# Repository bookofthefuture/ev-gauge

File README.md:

# ev-gauge
SoC, motor amps, motor/pack temp, 12V aux voltage, car mode and Zombieverter error
data over CANbus, on a single mode-aware display. For ESP32.

Copy `ev_gauge/secrets.h.example` to `ev_gauge/secrets.h` and fill in your home WiFi
SSID/password before flashing - the gauge runs its own `gaugedriver` AP and joins that
network at the same time, so OTA updates work both standalone and from your desk.

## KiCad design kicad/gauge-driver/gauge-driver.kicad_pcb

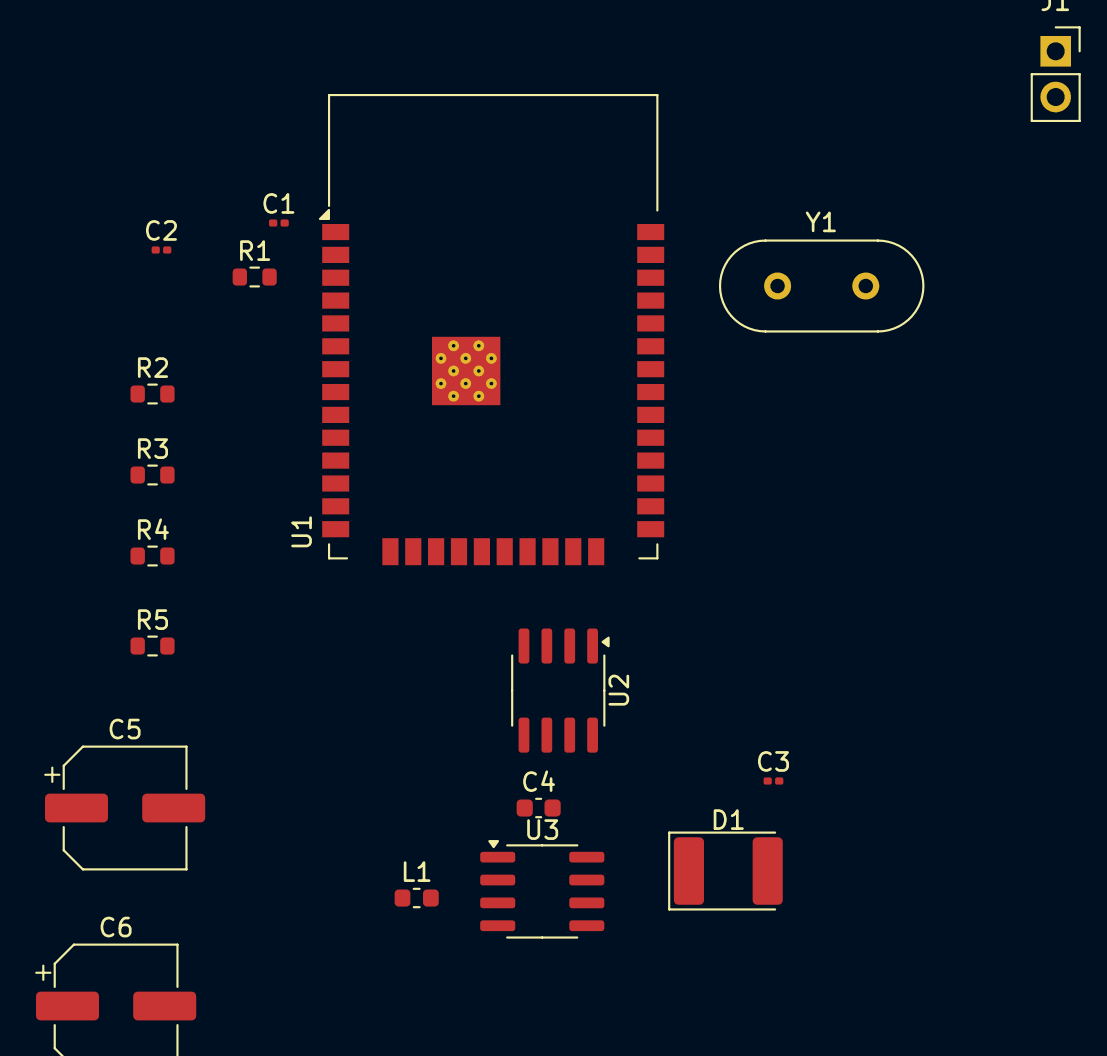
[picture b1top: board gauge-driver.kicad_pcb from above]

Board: 2 copper layers, 18 parts (0 on the bottom side), 14 nets, no tracks yet.

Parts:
C1: 22uF; C_0201_0603Metric
C2: 0.1uF; C_0201_0603Metric
C3: 1uF; C_0201_0603Metric
C4: C; C_0603_1608Metric
C5, C6: C_Polarized; CP_Elec_6.3x3
D1: D_Schottky; D_2114_3652Metric
J1: Conn_01x02_Socket; PinSocket_1x02_P2.54mm_Vertical
L1: L; L_0603_1608Metric
R1: 10k; R_0603_1608Metric
R2, R3, R4: R; R_0603_1608Metric
R5: 10K; R_0603_1608Metric
U1: ESP32-WROOM-32E; ESP32-WROOM-32D
U2: SN65HVD230; SOIC-8_3.9x4.9mm_P1.27mm
U3: LM2675M-3.3; SOIC-8_3.9x4.9mm_P1.27mm
Y1: Crystal; Crystal_HC18-U_Vertical

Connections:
/3v3: C1.1, C2.1, R1.1, U1.2 (VDD)
/CAN0_RXD: U1.24 (IO2), U2.4 (R)
/CAN0_TXD: U1.23 (IO15), U2.1 (D)
/Vin_12V: C5.1, U3.7 (VIN)
/Vout_3v3: C6.1, L1.2, U3.4 (FB)
GND: C1.2, C2.2, C3.2, C5.2, C6.2, D1.2 (A), R2.2, R3.2, R4.1, R4.2, R5.2, U1.1 (GND), U1.15 (GND), U1.38 (GND), U1.39 (GND), U2.2 (GND), U3.6 (GND), Y1.1, Y1.2
unnamed: C4.2, D1.1 (K), L1.1, U3.8 (VSW)
unnamed: J1.1, U2.7 (CANH)
unnamed: J1.2, U2.6 (CANL)
unnamed: C3.1, R1.2, U1.3 (EN)
unnamed: R2.1, U1.8 (IO32)
unnamed: R3.1, U1.9 (IO33)
unnamed: R5.1, U2.8 (Rs)
unnamed: C4.1, U3.1 (CB)

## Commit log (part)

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2022-06-30 format, font, flashing
    removed constant reset to black to avoid flashing
    resized fonts
    tweaked layout
    moved all text into functions
2023-10-21 added slimmed down version created for 38 pin esp32 dev module.
    Pared back graphics and added more controllability for pins
2023-10-21 Update ev_gauge_2023_v2.ino
    Changed pins for smaller esp32 layout and added line to prime reset switch, to avoid screen whiteout
2023-10-26 tidy up
2023-10-26 added 3d printing files
2023-10-26 added error handling to display for when no batteries connected
2023-10-28 Added pin options for 38 pin layout
2023-10-29 Added ElegantOTA for OTA updates
    Requires ElegantOTA library
2023-10-31 Updated OTA to async mode - NOT TESTED OTA YET!
2023-11-03 ota tweaks
2023-11-04 switched 30 pin can pins
    can't remember if I maybe transposed them and this is why can isn't working after OTA update
2023-11-04 tweaks to text positioning
2023-11-04 compiled bin file and added to repo
2023-11-04 tweaked can pin lauout and text spacing
2023-11-06 switched back to 30 pin
    Need to create a config option for this
2023-11-06 Added selector for 38 or 30 pin board and tidied up
2023-11-06 Now working
2023-11-13 added wire colours
    Sorry if you're using this - just for my own purposes
2023-11-14 added code to shut off error lights
    big thanks to Andy Powell for the sketch I adapted for this
2024-01-14 Revert "added wire colours"
    This reverts commit f70837c6e81b463de035a88e7492f9e43f48d391.
2024-01-18 first pass at heater info
    added in new filters and functions to update heater info on single display
2024-01-19 added pre-canbus heating symbols
2024-01-19 dual gauge layout
    simplified wiring and standardised on 30 pin module, added in dual display controls
2024-01-19 tweaked layout of soc
2024-02-26 Fixed can address for heater data
    also switched 'ERR' for '...' when soc over 100
2024-02-26 fixed can address for heater data
    also swapped 'err' for '...' when soc over 100
2024-04-27 imagereader
    added spiffs imagereader
2024-04-27 fixed loading image
2024-05-26 Update ev_gauge_2023_v2.ino
    added launch images and backlight ramp up and down
2024-05-26 error message and initial display
    added error message and can failure handling, and initial image display
2024-05-26 error handling tweaks
2024-05-26 debugging
2024-05-26 fixed screen rotation (needs testing)
2024-05-26 fixed screen clearing (untested)
2024-07-27 Update ev_gauge_2023_v2.ino
    cmmented out heating control
2024-12-17 added kicad files for hardware project
2024-12-20 Added cp2102
2024-12-22 updated cp2102 wiring
2025-02-16 reorganise for faster boot and reduced fade in delay
2025-02-16 kicad
2025-02-18 screwed up re-order
2025-02-18 Fixed re-ordering. Both screens now loading logo
2025-02-18 switched to taskscheduler
    moved functions for keeping display happy over to task scheduler and fixed some errors. tidied up code a bit.
2025-02-22 Moved CANbus pin to avoid upload issues
    No need to disconnect can transceiver when uploading now
2025-02-22 more cleanup and re-ordering
2025-02-23 minor tweaks
2025-02-24 increased pwm frequency
2025-02-24 tidied up folder and naming
2025-02-25 inverted displays - deleted old binary
2025-02-28 inverted startup logo
2025-03-02 switched to sending display data from heater driver not heater and reformatted display
2025-03-02 added custom icon font
    tweaked display to be tidier and show charging info
2025-03-04 modified soc processing for reduced flicker
2025-03-04 added custom font
2025-03-06 lots of tweaks to clean up data display
2025-03-07 removed other fonts - all uses ev_diy custom font now
2025-03-08 custom font
    Note: font needs to be copied to Fonts folder for Adafruit GFX Library
2025-03-08 Moved font to sketch folder
    Just for portability - also renamed font
2025-03-08 Improved readability for finding functions
2025-03-08 fixed wrong char issues & tweaked font size for soc
2025-03-09 rewrote heater_proc
2025-03-16 minor tweaks to fix soc_proc
2025-03-16 rewrote heater_proc because it wasn't working
